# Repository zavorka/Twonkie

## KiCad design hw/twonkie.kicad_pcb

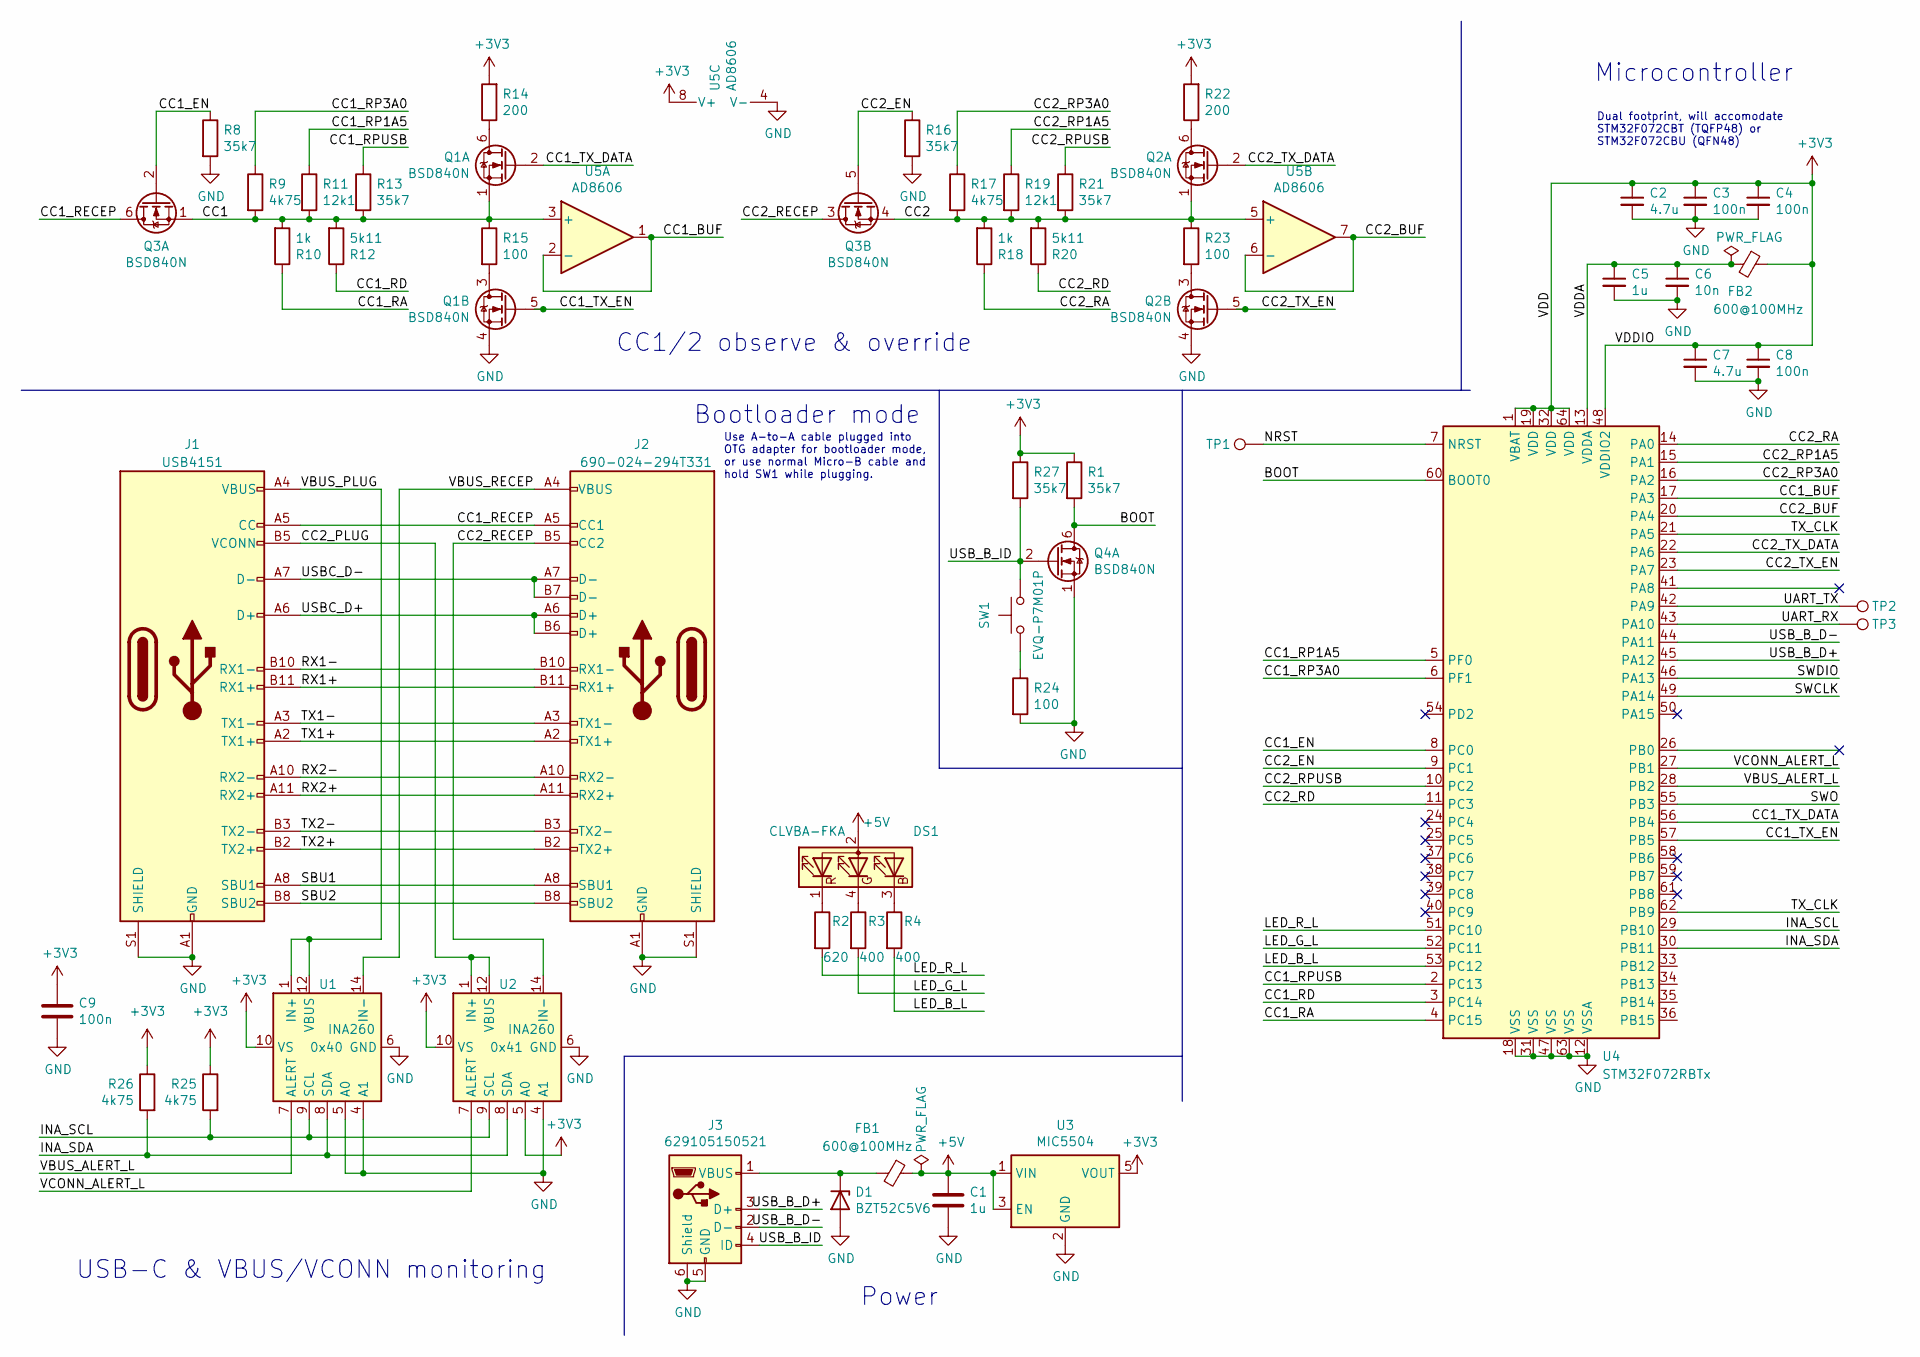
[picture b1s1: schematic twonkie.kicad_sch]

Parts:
C1, C5: 1u; C_0402_1005Metric; Mfg P/N CL05A105MQ5NNNC; DigiKey P/N 1276-1235-1-ND
C2, C7: 4.7u; C_0402_1005Metric; Mfg P/N CL05A475KQ5NRNC; DigiKey P/N 1276-1481-1-ND
C3, C4, C8, C9: 100n; C_0402_1005Metric; Mfg P/N CL05B104KA5NNNC; DigiKey P/N 1276-6720-1-ND
C6: 10n; C_0402_1005Metric; Mfg P/N CL05B103KB5NNNC; DigiKey P/N 1276-1028-1-ND
D1: BZT52C5V6; D_SOD-123; Mfg P/N BZT52C5V6-13-F; DigiKey P/N BZT52C5V6-13-FDICT-ND
DS1: CLVBA-FKA; LED_Cree-PLCC4_3.2x2.8mm_CCW; Mfg P/N CLVBA-FKA-CAEDH8BBB7A363; DigiKey P/N CLVBA-FKA-CAEDH8BBB7A363CT-ND
FB1, FB2: 600@100MHz; L_0402_1005Metric; Mfg P/N BLM15AG601SN1D; DigiKey P/N 490-1006-1-ND
J1: USB4151; USB_C_Plug_Wurth_632712000011; Mfg P/N USB4151-GF-C; DigiKey P/N 2073-USB4151-GF-CCT-ND
J2: 690-024-294T331; USB_C_Receptacle_Amphenol_12401548E4-2A; Mfg P/N 690-024-294T331; DigiKey P/N 151-1601-1-ND
J3: 629105150521; USB_Micro-B_Wuerth_629105150521; Mfg P/N 629105150521; DigiKey P/N 732-5960-1-ND
Q1, Q2, Q3, Q4: BSD840N; SOT-363_SC-70-6; Mfg P/N BSD840NH6327XTSA1; DigiKey P/N BSD840NH6327XTSA1CT-ND
R1, R8, R13, R16, R21, R27: 35k7; R_0402_1005Metric; Mfg P/N RC0402FR-0735K7L
R2: 620; R_0402_1005Metric; Mfg P/N RC0402FR-07620RL
R3, R4: 400; R_0402_1005Metric; Mfg P/N RC0402FR-07402RL
R9, R17, R25, R26: 4k75; R_0402_1005Metric; Mfg P/N RC0402FR-074K75L
R10, R18: 1k; R_0402_1005Metric; Mfg P/N RC0402FR-071KL
R11, R19: 12k1; R_0402_1005Metric; Mfg P/N RC0402FR-0712K1L
R12, R20: 5k11; R_0402_1005Metric; Mfg P/N RC0402FR-075K11L
R14, R22: 200; R_0402_1005Metric; Mfg P/N RC0402FR-07200RL
R15, R23, R24: 100; R_0402_1005Metric; Mfg P/N RC0402FR-07100RL
SW1: EVQ-P7M01P; SW_SPST_EVQP7C; Mfg P/N EVQ-P7M01P; DigiKey P/N P16770CT-ND
TP1, TP2, TP3: TestPoint; TestPoint_Pad_D1.0mm
U1, U2: INA260; TSSOP-16_4.4x5mm_P0.65mm; Mfg P/N INA260AIPWR; DigiKey P/N 296-47777-1-ND
U3: MIC5504; SOT-23-5; Mfg P/N MIC5504-3.3YM5-TR; DigiKey P/N 576-4764-1-ND
U4: STM32F072RBTx; LQFP-64_10x10mm_P0.5mm
U5: AD8606; MSOP-8_3x3mm_P0.65mm; Mfg P/N AD8606ARMZ-REEL; DigiKey P/N AD8606ARMZREELCT-ND

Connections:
+3V3: C2.1, C3.1, C4.1, C7.1, C8.1, C9.1, FB2.1, R1.1, R14.2, R22.2, R25.1, R26.1, R27.1, U1.10 (VS), U2.5 (A0), U2.10 (VS), U3.5 (VOUT), U4.1 (VBAT), U4.19 (VDD), U4.32 (VDD), U4.48 (VDDIO2), U4.64 (VDD), U5.8 (V+)
+5V: C1.1, DS1.2 (A), FB1.1, U3.1 (VIN), U3.3 (EN)
/BOOT: Q4.6 (D), R1.2, U4.60 (BOOT0)
/CC1: Q1.1 (S), Q3.1 (S), R9.2, R10.2, R11.2, R12.2, R13.2, R15.1, U5.3 (+)
/CC1_BUF: U4.17 (PA3), U5.1, U5.2 (-)
/CC1_EN: Q3.2 (G), R8.1, U4.8 (PC0)
/CC1_RA: R10.1, U4.4 (PC15)
/CC1_RD: R12.1, U4.3 (PC14)
/CC1_RECEP: J1.A5 (CC), J2.A5 (CC1), Q3.6 (D)
/CC1_RP1A5: R11.1, U4.5 (PF0)
/CC1_RP3A0: R9.1, U4.6 (PF1)
/CC1_RPUSB: R13.1, U4.2 (PC13)
/CC1_TX_DATA: Q1.2 (G), U4.56 (PB4)
/CC1_TX_EN: Q1.5 (G), U4.57 (PB5)
/CC2: Q2.1 (S), Q3.4 (S), R17.2, R18.2, R19.2, R20.2, R21.2, R23.1, U5.5 (+)
/CC2_BUF: U4.20 (PA4), U5.6 (-), U5.7
/CC2_EN: Q3.5 (G), R16.1, U4.9 (PC1)
/CC2_PLUG: J1.B5 (VCONN), U2.1 (IN+), U2.2 (IN+), U2.3 (IN+), U2.12 (VBUS)
/CC2_RA: R18.1, U4.14 (PA0)
/CC2_RD: R20.1, U4.11 (PC3)
/CC2_RECEP: J2.B5 (CC2), Q3.3 (D), U2.14 (IN-), U2.15 (IN-), U2.16 (IN-)
/CC2_RP1A5: R19.1, U4.15 (PA1)
/CC2_RP3A0: R17.1, U4.16 (PA2)
/CC2_RPUSB: R21.1, U4.10 (PC2)
/CC2_TX_DATA: Q2.2 (G), U4.22 (PA6)
/CC2_TX_EN: Q2.5 (G), U4.23 (PA7)
/INA_SCL: R25.2, U1.9 (SCL), U2.9 (SCL), U4.29 (PB10)
/INA_SDA: R26.2, U1.8 (SDA), U2.8 (SDA), U4.30 (PB11)
/LED_B_L: R4.2, U4.53 (PC12)
/LED_G_L: R3.2, U4.52 (PC11)
/LED_R_L: R2.2, U4.51 (PC10)
/NRST: TP1.1, U4.7 (NRST)
/RX1+: J1.B11 (RX1+), J2.B11 (RX1+)
/RX1-: J1.B10 (RX1-), J2.B10 (RX1-)
/RX2+: J1.A11 (RX2+), J2.A11 (RX2+)
/RX2-: J1.A10 (RX2-), J2.A10 (RX2-)
/SBU1: J1.A8 (SBU1), J2.A8 (SBU1)
/SBU2: J1.B8 (SBU2), J2.B8 (SBU2)
/SWCLK: U4.49 (PA14)
/SWDIO: U4.46 (PA13)
/SWO: U4.55 (PB3)
/TX1+: J1.A2 (TX1+), J2.A2 (TX1+)
/TX1-: J1.A3 (TX1-), J2.A3 (TX1-)
/TX2+: J1.B2 (TX2+), J2.B2 (TX2+)
/TX2-: J1.B3 (TX2-), J2.B3 (TX2-)
/TX_CLK: U4.21 (PA5), U4.62 (PB9)
/UART_RX: TP3.1, U4.43 (PA10)
/UART_TX: TP2.1, U4.42 (PA9)
/USBC_D+: J1.A6 (D+), J2.A6 (D+), J2.B6 (D+)
/USBC_D-: J1.A7 (D-), J2.A7 (D-), J2.B7 (D-)
/USB_B_D+: J3.3 (D+), U4.45 (PA12)
/USB_B_D-: J3.2 (D-), U4.44 (PA11)
/USB_B_ID: J3.4 (ID), Q4.2 (G), R27.2, SW1.1
/VBUS_ALERT_L: U1.7 (ALERT), U4.28 (PB2)
/VBUS_PLUG: J1.A4 (VBUS), J1.A9 (VBUS), J1.B4 (VBUS), J1.B9 (VBUS), U1.1 (IN+), U1.2 (IN+), U1.3 (IN+), U1.12 (VBUS)
/VBUS_RECEP: J2.A4 (VBUS), J2.A9 (VBUS), J2.B4 (VBUS), J2.B9 (VBUS), U1.14 (IN-), U1.15 (IN-), U1.16 (IN-)
/VCONN_ALERT_L: U2.7 (ALERT), U4.27 (PB1)
/VDDA: C5.1, C6.1, FB2.2, U4.13 (VDDA)
GND: C1.2, C2.2, C3.2, C4.2, C5.2, C6.2, C7.2, C8.2, C9.2, D1.2 (A), J1.A1 (GND), J1.A12 (GND), J1.B1 (GND), J1.B12 (GND), J1.S1 (SHIELD), J1.S2 (SHIELD), J1.S3 (SHIELD), J1.S4 (SHIELD), J1.S5 (SHIELD), J1.S6 (SHIELD), J2.A1 (GND), J2.A12 (GND), J2.B1 (GND), J2.B12 (GND), J2.S1 (SHIELD), J2.S2 (SHIELD), J2.S3 (SHIELD), J2.S4 (SHIELD), J2.S5 (SHIELD), J2.S6 (SHIELD), J2.S7 (SHIELD), J2.S8 (SHIELD), J3.5 (GND), J3.6 (Shield), Q1.4 (S), Q2.4 (S), Q4.1 (S), R8.2, R16.2, R24.2, U1.4 (A1), U1.5 (A0), U1.6 (GND), U1.11 (GND), U2.4 (A1), U2.6 (GND), U2.11 (GND), U3.2 (GND), U4.12 (VSSA), U4.18 (VSS), U4.31 (VSS), U4.47 (VSS), U4.63 (VSS), U5.4 (V-)
unnamed: D1.1 (K), FB1.2, J3.1 (VBUS)
unnamed: DS1.1 (RK), R2.1
unnamed: DS1.3 (BK), R4.1
unnamed: DS1.4 (GK), R3.1
unnamed: Q1.3 (D), R15.2
unnamed: Q1.6 (D), R14.1
unnamed: Q2.3 (D), R23.2
unnamed: Q2.6 (D), R22.1
unnamed: R24.1, SW1.2

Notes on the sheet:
Bootloader mode
Dual footprint, will accomodate STM32F072CBT (TQFP48) or STM32F072CBU (QFN48)
Power
Use A-to-A cable plugged into OTG adapter for bootloader mode, or use normal Micro-B cable and hold SW1 while plugging.
Microcontroller
USB-C & VBUS/VCONN monitoring
CC1/2 observe & override

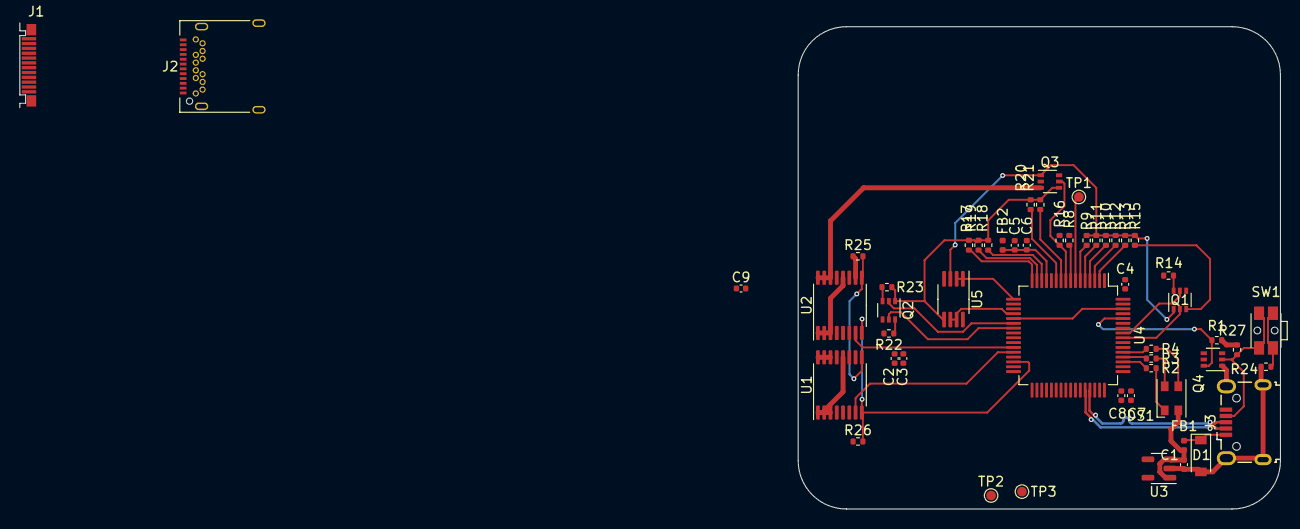
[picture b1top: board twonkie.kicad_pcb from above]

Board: 4 copper layers, 130.7 x 50.4 mm, 53 parts (0 on the bottom side), 65 nets.
